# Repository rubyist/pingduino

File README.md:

# Pingduino

Pingduino an Arduino based score keeper for games of ping pong. This repository
contains everything you need to build your own. Except the hardware, of course!

## Features

Pingduino is set up such that there are two scoring buttons and a display. I've
mounted the buttons underneath my ping pong table, one on each side. When a player
scores, they press their button.

The display is built to show each score and an indicator showing whose who is
currently serving. The serve indicator updates automatically as scores are input.

The program code contains game winning logic, meaning it knows the rules of
ping pong and will indicate the winner when it detects the game has been won.

Upon detecting a win, Pingduino will play a victory song and flash the serve
indicator of the game winner.

If Pingduino detects no activity for 20 minutes it will automatically turn off
the display lights and the scoring button lights. Pressing any button will wake
the display and Pingduino will pick up where you left off.

## Usage Instructions

Once you've built and installed Pingduino it's time to play! Simply start playing
ping pong. Pingduino lets you know which player should serve. If you score, press
your button. Eventually somebody will win!

Once the game has been won, the player who will serve the next game will reset
the system by doing a long press (press and hold for a second or two) on their
button.

## Building Your Own

Building your own Pingduino should be easy. It's my first Arduino project and
I'm a pretty novice hardware hacker. This repository contains the program code
to load onto the Arduino as well as schematics, a parts list, and a PCB layout
should you choose to go beyond the breadboard. Once completed I'll post a link
to pictures of my build process.

### Display

I was initially going to use some giant ~8" 7-segment LEDs for the score display,
however the two that I found that were big enough were too expensive and not well
built or out of stock. I decided to build my own large 7-segment displays out of
ping pong balls and individual LEDs. Once assembled, these behave pretty much like
regular 7-segment displays and I'm driving them with 4 shift registers chained
together.

I've kept the display logic code fairly encapsulated so that you can be free to
implement whatever kind of display you'd like. My intitial prototypes were built
using an LCD display.

### Scoring Buttons

There are scoring buttons mounted under each side of the table. I used some
[big dome push buttons](https://www.sparkfun.com/products/11275) from Sparkfun.
These are pretty big, you could certainly get away with much smaller buttons,
but I ordered them so I rolled with it.

To connect the buttons to the main module I used some 1/8" audio jacks and cables.
These are readily available, cheap, and perfectly support the button signal and
a line to light the LED in the button.

To mount the buttons under the table I designed and printed some simple boxes.
You can find the openscad and stl files in the models directory. I printed these
on a Makerbot Replicator 2. It's just a box that goes under a table so you can
get away with printing at a lower resolution (0.3mm), but be aware that the hole
for the audio jack will probably have to be drilled and smoothed out some before
it fits nicely.

## Contributing

Got an idea for improving Pingduino? Found a bug? I'd love to know about it!
Simply file an issue or open a pull request here on GitHub.

If you build and use a Pingduino I'd love to know about it, especially if you
come up with a different kind of display.

## License

Everything in this repo is released under the MIT license.

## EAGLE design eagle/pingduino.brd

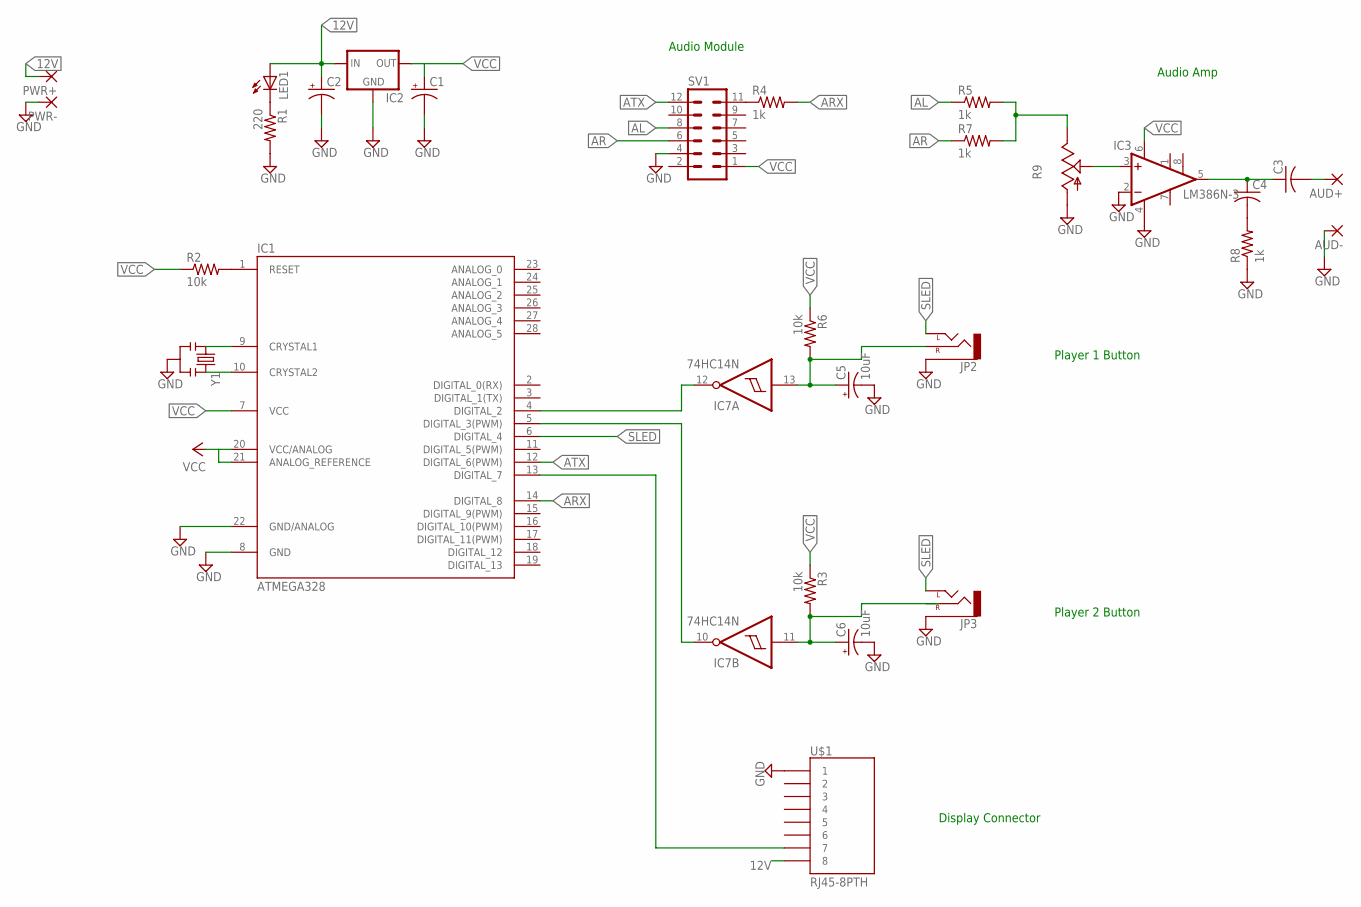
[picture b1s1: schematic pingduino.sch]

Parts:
AUD+: WIREPAD2,15/1,0; 2,15/1,0
AUD-: WIREPAD2,15/1,0; 2,15/1,0
C1, C2: CAP_POLPTH2; CPOL-RADIAL-10UF-25V
C3, C4: C-US050-024X044; C050-024X044
C5, C6: 10uF; CPOL-RADIAL-10UF-25V
IC1: ATMEGA328; DIL28-3
IC2: V_REG_78XX-TO-220; TO-220-ALT
IC3: LM386N-3; DIL08
IC7: 74HC14N; DIL14
JP2, JP3: AUDIO-JACKPTH; AUDIO-JACK
LED1: LED3MM
PWR+: WIREPAD2,15/1,0; 2,15/1,0
PWR-: WIREPAD2,15/1,0; 2,15/1,0
R1: 220; 0204/7
R2, R3, R6: 10k; 0204/7
R4, R5, R7, R8: 1k; 0204/7
R9: TRIM_US-B25U; B25U
SV1: MA06-2
U$1: RJ45-8PTH; RJ45-8
Y1: RESONATORPTH; RESONATOR-PTH

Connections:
12V: C2.1 (+), IC2.IN, LED1.A, PWR+.1, U$1.8
AL: R5.1, SV1.8
AR: R7.1, SV1.6
ARX: IC1.13 (DIGITAL_7), IC1.14 (DIGITAL_8), R4.2, U$1.7
ATX: IC1.12 (DIGITAL_6(PWM)), SV1.12
GND: AUD-.1, C1.2 (-), C2.2 (-), C5.2 (-), C6.2 (-), IC1.8 (GND), IC1.22 (GND/ANALOG), IC2.GND, IC3.2 (-IN), IC3.4 (GND), IC7.7 (GND), JP2.SLEEVE, JP3.SLEEVE, PWR-.1, R1.2, R8.1, R9.A, SV1.4, U$1.1, Y1.2
unnamed: IC1.10 (CRYSTAL2), Y1.3
unnamed: IC1.9 (CRYSTAL1), Y1.1
unnamed: LED1.K (C), R1.1
unnamed: IC1.1 (RESET), R2.2
unnamed: IC1.4 (DIGITAL_2), IC7.12 (O)
unnamed: C6.1 (+), IC7.11 (I), R3.2
unnamed: IC1.5 (DIGITAL_3(PWM)), IC7.10 (O)
unnamed: C5.1 (+), IC7.13 (I), JP2.RING (RIGHT), R6.2
unnamed: R4.1, SV1.11
unnamed: R5.2, R7.2, R9.E
unnamed: IC3.3 (+IN), R9.S
unnamed: C3.1, C4.1, IC3.5 (OUT)
unnamed: C4.2, R8.2
unnamed: AUD+.1, C3.2
SLED: IC1.6 (DIGITAL_4), JP2.TIP (LEFT), JP3.TIP (LEFT)
VCC: C1.1 (+), IC1.7 (VCC), IC1.20 (VCC/ANALOG), IC1.21 (ANALOG_REFERENCE), IC2.OUT, IC3.6 (VS), IC7.14 (VCC), R2.1, R3.1, R6.1, SV1.1

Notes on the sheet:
Player 1 Button
Player 2 Button
Display Connector
Audio Module
Audio Amp

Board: 2 copper layers, 29 parts (0 on the bottom side), 22 nets, no tracks yet.

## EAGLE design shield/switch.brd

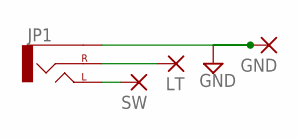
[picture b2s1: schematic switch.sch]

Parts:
GND: 2,15/1,0
JP1: AUDIO-JACKPTH; AUDIO-JACK
LT: 2,15/1,0
SW: 2,15/1,0

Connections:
GND: GND.1, JP1.SLEEVE
unnamed: JP1.RING (RIGHT), LT.1
unnamed: JP1.TIP (LEFT), SW.1

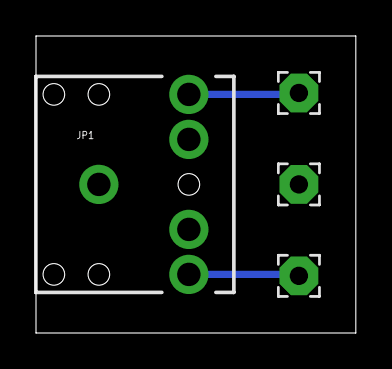
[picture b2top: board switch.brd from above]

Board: 2 copper layers, 17.8 x 16.5 mm, 4 parts (0 on the bottom side), 3 nets.

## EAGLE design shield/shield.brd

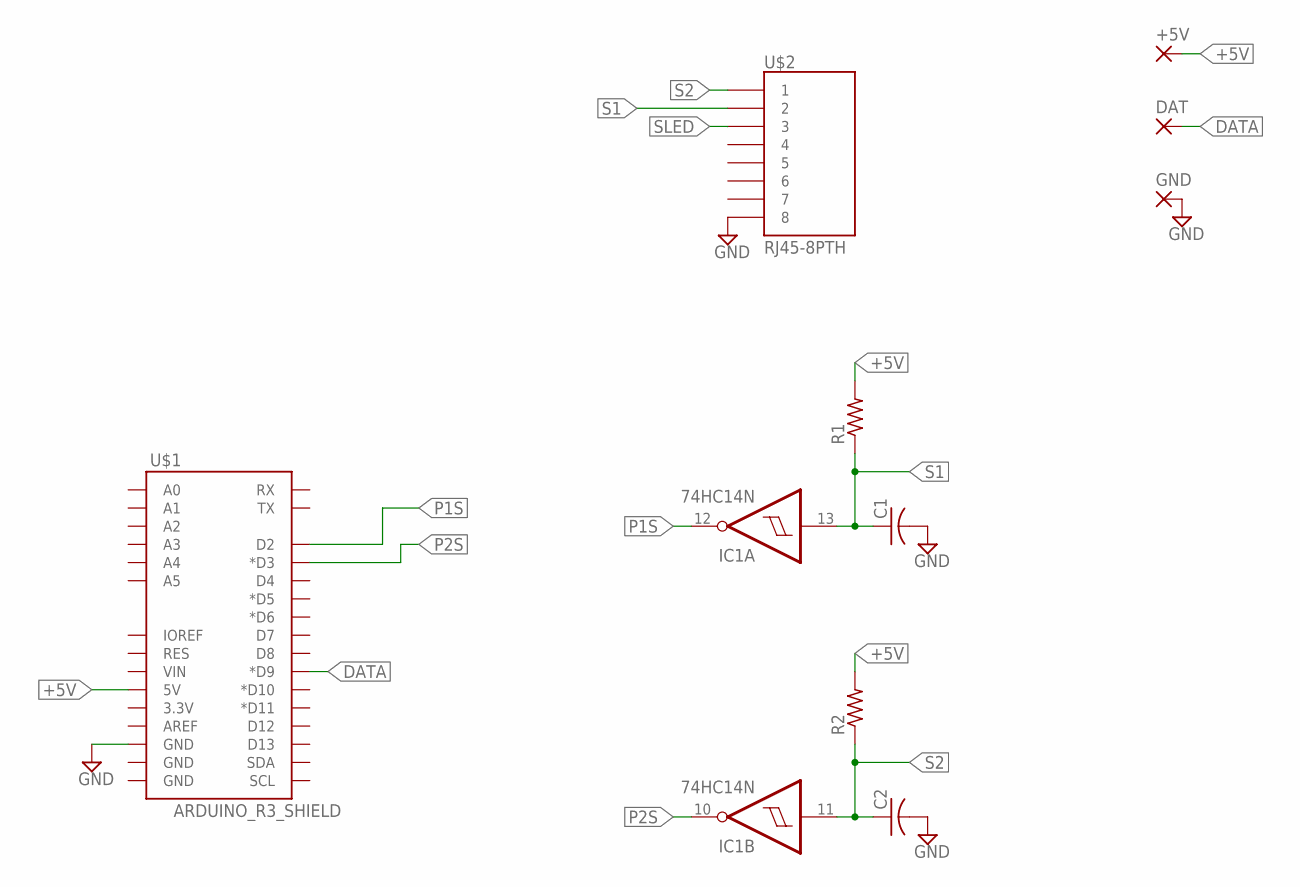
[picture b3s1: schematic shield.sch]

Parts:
+5V: WIREPAD2,15/1,0; 2,15/1,0
C1, C2: C-US025-025X050; C025-025X050
DAT: WIREPAD2,15/1,0; 2,15/1,0
GND: WIREPAD2,15/1,0; 2,15/1,0
IC1: 74HC14N; DIL14
R1, R2: R-US_0207/7; 0207/7
U$1: ARDUINO_R3_SHIELD; UNO_R3_SHIELD
U$2: RJ45-8PTH; RJ45-8

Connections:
+5V: +5V.1, R1.2, R2.2, U$1.5V
DATA: DAT.1, U$1.D9 (*D9)
GND: C1.2, C2.2, GND.1, IC1.7 (GND), U$1.GND@2 (GND), U$2.8
P1S: IC1.12 (O), U$1.D2
P2S: IC1.10 (O), U$1.D3 (*D3)
S1: C1.1, IC1.13 (I), R1.1, U$2.2
S2: C2.1, IC1.11 (I), R2.1, U$2.1
SLED: U$2.3
VCC: IC1.14 (VCC)

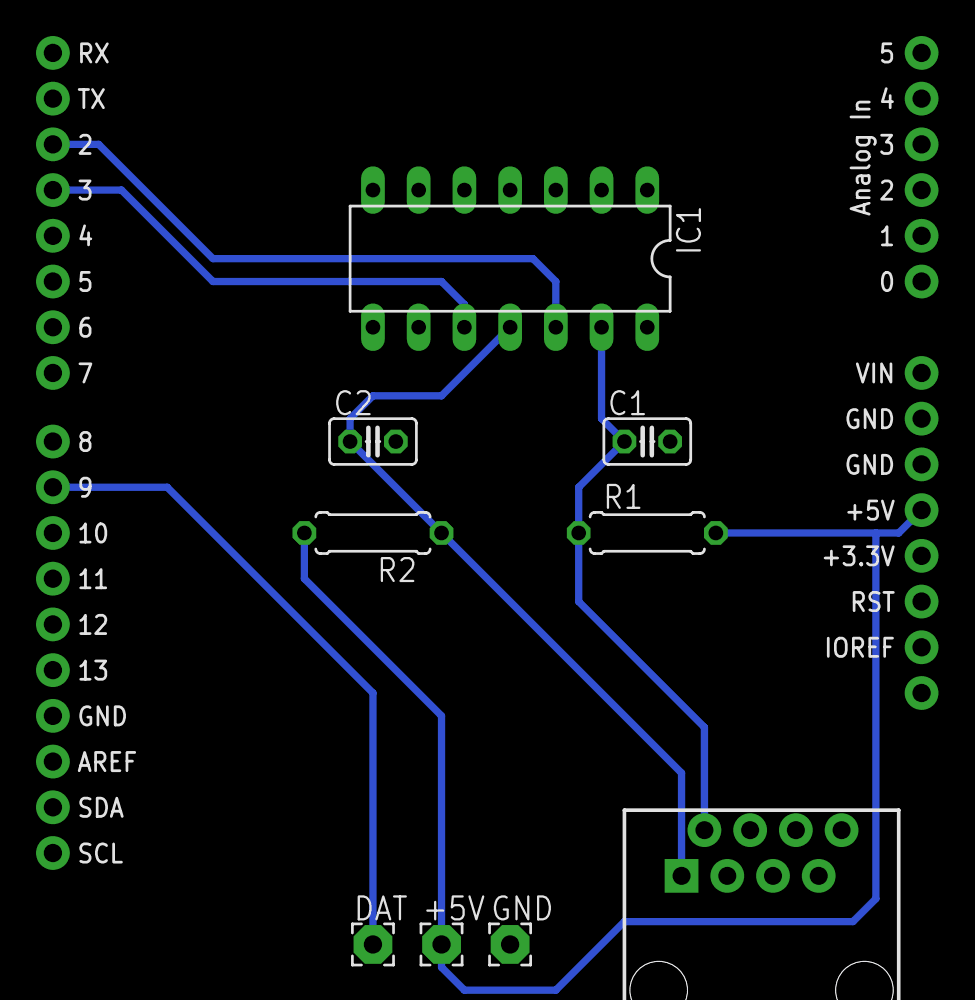
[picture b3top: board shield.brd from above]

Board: 2 copper layers, 10 parts (0 on the bottom side), 7 nets.

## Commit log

2013-12-22 Count button presses for score tracking
2013-12-22 basic game winning rule
2013-12-22 add some delay, remove old flag
2013-12-22 oo'ify button handlers
2013-12-22 reset game with long press
2013-12-22 Use an LCD display for now
2013-12-23 victory song
2013-12-23 Keep track of serves
2014-01-04 Remove LCD code, use shift register based display (p1 only right now)
2014-01-04 Blink winning player's serve indicator (p1 only at the moment)
2014-01-04 Blank the display after 10 minutes of inactivity
2014-01-04 Put button lights on pins, sleep/wake them up too
2014-01-04 start readme, add license
2014-01-06 Rename directory and ino file
2014-01-06 import eagle schematics
2014-01-07 gitignore
2014-01-07 Fix display connectors on schematic
2014-01-07 First attempt at pcb layout
2014-01-08 Re-route the 5x2 headers so I can actually solder them.
2014-01-11 Convert the code to the current schematic, use of hardware interrupts
2014-01-11 Properly display p2 score
2014-01-11 Shift out enough bytes to make sure the score fully blanks
2014-01-11 Start factoring out game and display logic for cleaner code.
    Also factor out VictorySong to get it out of the way.
2014-01-11 Reestablish server tracking
2014-01-11 Have Game::init just call restart(1)
2014-01-11 Handle game over / reset
2014-01-11 Play the victory song!
2014-01-11 Reenable sleep mode, remove commented out code
2014-01-11 Fix setting server on restart
2014-01-11 Remove serial printing
2014-01-11 Blink the serve indicator of the winning player
2014-01-11 Don't reset the variable before you pass it in to game.reset() ...
2014-01-11 When game is reset, interrupt the victory song
2014-01-11 Create gh-pages branch via GitHub
2014-01-17 Start work on schematics/board for an arduino shield version with a different display idea
2014-01-19 Sketchup model for under table switch mount
2014-01-19 Board/Schematic for switch mounts
2014-01-19 fix ground plane routing on switch mount board
2014-01-21 First pass at incorporating WaveHC and Wave Shield
2014-01-21 Initialize serial bus for debug logging
2014-01-21 Stop the song on reset, make sure song can play again
2014-01-21 Remove unused cruft
2014-01-21 Make played flag volatile
2014-01-21 player one score on the led strip
2014-01-21 Move victory song back into its own files
2014-01-22 Display functions for all players.
    - use 2 leds per segment
    - disable button leds for now, I think it's drawing too much current
2014-01-24 Use polling for buttons as interrupts were problematic with the wave shield
2014-01-24 Double pressing a button will decrement the score
2014-01-24 I don't know how that happened ...
2014-01-24 Don't modify the scores if the game is over. Closes #19
2014-01-24 Allow mid-game reset. Closes #11
2014-01-24 Fix sleep and wake up
2014-01-24 stop leaving test values in the code
2014-01-25 Start a redo of the switch mount in openscad
2014-01-25 more mounts, fix screws
2014-01-25 mounting screws
2014-01-25 Comments, STL exports for mount body and cover
2014-01-25 remove old sketchup model
2014-01-25 Thinner walls
2014-01-25 Vanity
2014-01-25 Show body by default
2014-01-25 Add some commenting to the switch mount scad file
2014-01-25 Correct hole diameter in button box
2014-01-26 remove unused code
2014-01-26 Add a couple supports midway up the box
2014-01-26 Remove name printing
2014-01-26 Need a little extra padding for my table
2014-01-26 Update stl files
2014-01-26 Readme blurb about the buttons and boxes
2014-01-30 Display segment scad file
2014-01-30 enshorten the segments a bit
2014-01-30 segment stl
2014-02-08 Designate debug serial prints vs game play A Raspberry Pi or other device can be hooked to the serial port and watch for these events. This can be used to track statistics, provide a web app, tournam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
2014-02-08 Update segment model
2014-02-22 Add Garan audio module and amplifier to schematic and board
2014-02-24 Start code for using garan audio module to play victory song
2014-02-24 Start and stop the audio as needed
2014-03-03 Start a port to ATtiny85 - here's the display code
2014-03-05 Rudimentary scoring button code Does not yet contain the state machine for short/long/double pressing
2014-03-05 update gitignore
2014-03-05 turn on the score button leds
2014-03-07 Sketch in button handling, still needs timer work

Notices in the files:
parts and their libraries:
SparkFun-PowerIC: Licensing: CC v3.0 Share-Alike You are welcome to use this library for commercial purposes.
